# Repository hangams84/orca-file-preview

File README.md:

[한국어](README.md) · [English](README.en.md) · [简体中文](README.zh-CN.md) · [繁體中文](README.zh-TW.md) · [日本語](README.ja.md) · [Deutsch](README.de.md) · [Français](README.fr.md) · [Español](README.es.md) · [Português (Brasil)](README.pt-BR.md) · [Русский](README.ru.md) · [Türkçe](README.tr.md)

# File Preview for Orca

File Preview는 [Orca](https://github.com/stablyai/orca) 안에서 Office · 한글 · PDF · 텍스트 · 이미지 · 3D · CAD · 전자 설계 파일을
**읽기 전용으로 미리 보여 주는** 플러그인입니다. Orca 데스크톱(Windows · macOS · Linux)과 브라우저/모바일 클라이언트에서 동작합니다.

- 최신 릴리스: **v0.4.0** · Orca **1.4.248** 이상 필요 (Git URL 설치는 **1.4.252** 이상)
- `sandboxed-ui` 방식으로만 실행됩니다. 추가 권한(capability)이나 네트워크 접근을 사용하지 않으며, 파일을 수정하지도 않습니다.

## 지원 형식

| 형식 | 확장자 | 엔진 · 표시 내용 |
| --- | --- | --- |
| Word | `.docx` `.doc` | docx-preview · 자체 OLE/CFB 파서 (RTF·HTML·DOCX로 저장된 `.doc` 자동 감지) |
| PowerPoint | `.pptx` `.ppt` | 자체 OOXML 렌더러 · 자체 PPT 레코드 파서 |
| Excel | `.xlsx` `.xlsm` `.xls` `.ods` | SheetJS CE (Web Worker, 수식 계산 대체, 가상 스크롤) |
| 한글 문서 | `.hwp` `.hwpx` | HWP 5 · HWPX(OWPML)를 한글이 저장한 줄 배치대로 표시. 배포용·암호 문서와 HWP 3은 안내 메시지 표시 |
| PDF | `.pdf` | pdf.js (지연 렌더링, 한글 CMap, 암호 입력) |
| 이미지 | `.gif` `.bmp` `.svg` | 브라우저 디코더 (SVG 스크립트 차단, 배경 선택) |
| 웹 | `.html` `.htm` `.xhtml` | DOMPurify + 샌드박스 iframe (스크립트 미실행) |
| 표 | `.csv` `.tsv` | 자체 RFC 4180 파서 (인코딩·구분자 감지, 정렬, 필터) |
| 텍스트 | `.txt` `.log` | 인코딩 감지 (UTF-8/16, EUC-KR 등), 줄 번호, 자동 줄바꿈 |
| 다이어그램 | `.drawio` `.dio` `.vsdx` `.vsdm` `.vstx` `.vssx` | 자체 SVG 렌더러: draw.io(압축·여러 페이지, 기본 도형·연결선·스타일, HTML 레이블은 DOMPurify로 정제), Visio(마스터·스타일 시트 상속, Geometry 행 전체, 그룹·연결선·텍스트 서식·채우기 패턴·그라데이션·테마·EMF/WMF 그림·배경 페이지). 페이지 선택, 이동·확대·맞춤, 어두운 캔버스, 링크 |
| 3D 모델 | `.stl` `.obj` `.ply` `.glb` `.gltf` `.3mf` `.off` `.fbx` `.dae` | three.js (WebGL, 회전·확대·이동, 터치, Draco·meshopt, Web Worker 파싱). OBJ의 `.mtl`·텍스처, glTF의 외부 `.bin`·이미지, DAE·FBX·3MF 텍스처는 참조 파일(📁 · 끌어 놓기)에서 읽음 |
| CAD (B-rep) | `.step` `.stp` `.stpz` `.iges` `.igs` `.brep` | OpenCascade (occt-import-js, WebAssembly, Web Worker): 어셈블리·부품 목록·색상, 테셀레이션 품질 선택. `.stpz`는 gzip으로 압축한 STEP |
| CAD 2D 도면 | `.dxf` `.dwf` `.dwfx` | 자체 Canvas 2D 렌더러: DXF(ASCII·바이너리, R12–2018+, 블록·치수·해치·MTEXT·한글), DWF(W2D 스트림, 시트, 썸네일 대체), DWFx(XPS 페이지, 내장 글꼴). 레이어 목록, 모형·배치(뷰포트)·시트 선택, 밝은/어두운 배경, 정보 표시줄. DXF 외부 참조(xref)와 IMAGE 엔터티는 참조 파일에서 읽음 (xref 레이어는 `XREF\|레이어`) |
| AutoCAD 도면 (별도 플러그인) | `.dwg` `.dwt` | **File Preview DWG** — [별도 저장소](https://github.com/hangams84/orca-file-preview-dwg), GPL-3.0-or-later, 따로 설치합니다 (Git URL `https://github.com/hangams84/orca-file-preview-dwg.git`, 소스 [dwg-plugin/](dwg-plugin/README.md)). LibreDWG (WebAssembly, Web Worker) + Canvas: 모형/배치, 레이어, 블록, 한글 문자, 치수, 해치 |
| 로봇 모델 (ROS) | `.urdf` `.xacro` | 자체 XML 리더 + xacro 처리기(ROS 2 xacro 2.x 규칙, eval 없는 안전한 식 계산기) + three.js: 기구학 트리, 기본 형상, 원점·재질, 조인트 6종·한계·mimic, 조인트 슬라이더, 외형/충돌/좌표계/조인트 축 표시. `.urdf.xacro`도 엽니다. 메시와 `xacro:include`는 참조 파일에서 읽음 |
| KiCad | `.kicad_sch` `.kicad_pcb` `.kicad_mod` `.kicad_sym` `.kicad_pro` `.kicad_wks` | 자체 S-expression 파서 + SVG 렌더러 (KiCad 6–10, 스트로크 글꼴 newstroke): 회로도, PCB(레이어 표시/숨김, 앞/뒷면 뒤집기), 풋프린트, 심볼 라이브러리, 프로젝트 요약, 패드·핀·넷 정보 툴팁. 프로젝트 폴더를 지정하면 계층 시트 탐색과 사용자 도면 틀 표시 |
| SolidWorks | `.sldprt` `.sldasm` `.slddrw` `.slddrt` `.prtdot` `.asmdot` `.drwdot` | 자체 컨테이너 리더 (2014 이전 OLE/CFB, 2015 이후 형식): 저장된 미리보기 그림, 파트의 표시 메시(3D), **어셈블리 3D**(저장된 배치 + 메시, 없으면 📁로 지정한 파트 파일), 속성·구성·참조 파일·피처 이름·저장 기록 |
| EPLAN Electric P8 | `.edz` `.zw1` `.elk` `.ell` `.elr` `.els` `.ela` `.elp` `.elx` `.zx1` `.ema` `.emp` | 자체 7z(LZMA/LZMA2)·ZIP 리더: EDZ 부품 데이터·그림·PDF 문서, **매크로 그래픽**(PXF: 선·호·곡선·문자, 변형별), 프로젝트 백업의 속성·페이지 설명·**부품 목록**·그림·내용 트리, 링크 파일 + 📁 프로젝트 폴더(`.edb`) |
| AI 모델 (PyTorch) | `.pt` `.pth` `.ckpt` `.chkpt` `.pt2` `.ptl` `.safetensors` | 코드를 **실행하지 않는** 자체 pickle 해석기: state_dict·통째 저장한 모듈·TorchScript·torch.export·Lightning 체크포인트·레거시 pickle, safetensors. 보기 7종(**연산 그래프**·모듈 트리·레이어 표·파라미터 맵·아키텍처 도식(추론)·**텐서 검사기**·체크포인트 정보)과 SVG/PNG/JSON/Markdown 내보내기. File Preview 패널은 범위 읽기로 GB 단위 파일도 열고, 내용으로 판별한 bin·pkl 파일도 엽니다 |
| AI 모델 (ONNX·TFLite·GGUF·Keras·NumPy) | `.onnx` `.tflite` `.gguf` `.keras` `.h5` `.hdf5` `.npy` `.npz` | 같은 보기로 표시: ONNX·TFLite·Keras 연산 그래프, GGUF 메타데이터와 양자화 텐서(Q4_K 등) 값, HDF5·NumPy 배열. ONNX 외부 데이터는 📁 폴더로 연결 |
| (읽을 수 없는 파일) | 위 형식 전체 | 일반 검사기: 형식 식별, 크기, 엔트로피, 16진수 덤프, 문자열 |
| **File Preview 패널** | 위 형식 전체 | 오른쪽 사이드바 패널. 아래 [File Preview 패널](#file-preview-패널) 참고 |

공통: 다크/라이트 테마 실시간 반영, 한국어/영어 UI, Ctrl+휠 · 핀치 · 버튼으로 확대/축소, 휴대폰 화면 폭 맞춤,
파일이 바뀌면 자동 갱신, 손상된 파일은 친절한 오류 안내.

### 텍스트 형식도 바로 미리보기로 열립니다 (0.4.0)

URDF·xacro, KiCad, draw.io, ASCII DXF, STEP·IGES·BREP, OBJ 등 텍스트로 된 3D 형식, RTF/HTML로 저장된 `.doc`,
XML `.xls`는 Orca가 텍스트 파일로 인식합니다. 플러그인이 이러한 파일용 텍스트 편집기를 따로 등록하므로 이제 기본적으로
미리보기로 열립니다. 단, Orca가 직접 여는 형식(`.txt` `.csv` `.tsv` `.html` `.htm`)은 Orca 규칙에 따라 ‘소스’ 보기로 먼저 열립니다.
탭 오른쪽 위의 보기 전환 버튼에서 미리보기를 선택하면 됩니다.

### 참조 파일 (📁 · 끌어 놓기)

Orca는 편집기에 연 파일 하나만 플러그인에 전달합니다. 툴바의 📁 버튼으로 폴더를 선택하거나(Shift를 누른 채 누르면 파일 선택) 파일을 미리보기에
끌어다 놓으면, 플러그인이 샌드박스 프레임 안에서 그 파일들을 함께 읽습니다.

| 미리보기 | 폴더나 파일을 지정하면 추가되는 기능 |
| --- | --- |
| 로봇 (URDF/xacro) | 메시(STL, 텍스처가 있는 DAE, `.mtl`이 있는 OBJ, glTF)가 자리 표시자를 대체하고 조인트 자세는 유지. `xacro:include` 처리(`$(find pkg)`, 상대 경로, 중첩) |
| 3D | OBJ 재질과 텍스처, glTF 외부 `.bin`과 이미지, DAE 텍스처 |
| CAD 도면 (DXF) | 외부 참조(xref)를 `XREF\|레이어`로 삽입, IMAGE 엔터티 표시 |
| KiCad | 하위 시트 탐색(인스턴스별 참조 기호), `.kicad_pro` → 회로도·보드, 사용자 `.kicad_wks` |
| SolidWorks | 저장된 배치로 **어셈블리 3D** 표시 (2015 이후 파일은 파트 파일 불필요, 2014 파일은 지정한 파트 파일 사용) |
| EPLAN | 매크로 그래픽 표시(`.ema` `.emp`, `.edz` 안의 매크로), `.elk` + `.edb` 폴더 → 프로젝트 속성, 페이지, 부품 목록 |

### File Preview 패널

오른쪽 사이드바의 **File Preview** 패널에서 "파일 열기…", "폴더 열기…" 또는 끌어 놓기로 파일을 열면 같은 렌더러로 표시합니다.
Orca 편집기의 50 MB 한도가 적용되지 않으며(렌더러 자체 한도만 적용, 최대 1 GB) 워크스페이스 밖의 파일도 열 수 있습니다. 함께 연 파일은
참조 파일로 사용됩니다. 추가 권한은 필요하지 않습니다.

## 설치

### (a) Orca 앱에서 설치 (권장)

Orca **1.4.252** 이상에서 사용할 수 있습니다.

1. **설정** → **플러그인**을 엽니다.
2. **플러그인 추가** → **Git URL에서…**를 선택합니다.
3. **저장소 URL**에 `https://github.com/hangams84/orca-file-preview.git`을 붙여 넣고 **계속** → **설치**를 누릅니다.
4. Orca가 보여 주는 권한(샌드박스 화면 표시만)을 확인하고 **플러그인 활성화**를 누릅니다.

화면별 안내: [docs/install-guide/ko.md](docs/install-guide/ko.md)

<!-- install-guide-thumbs -->

`.dwg` · `.dwt` 미리보기가 필요하면 같은 방법으로 `https://github.com/hangams84/orca-file-preview-dwg.git`도 설치합니다.

### (b) CLI로 설치

```sh
# GitHub에서 최신 버전 설치 (Orca 1.4.252+). Orca가 요청 권한과 승인 지문을 출력합니다.
orca plugin install https://github.com/hangams84/orca-file-preview
orca plugin install https://github.com/hangams84/orca-file-preview --approve <fingerprint>
# 특정 버전: https://github.com/hangams84/orca-file-preview#v0.5.0

# 또는 로컬 폴더
orca plugin install ./plugin
```

### (c) 릴리스 패키지 · 실행 파일 · 스크립트

[GitHub Releases](https://github.com/hangams84/orca-file-preview/releases)에서 내려받습니다. Orca 1.4.248 이상이 설치되어 있고
한 번 이상 실행된 PC가 필요하며, 관리자 권한은 필요 없습니다. 모든 설치 프로그램은 Orca가 요청하는 권한을 보여 주고,
사용자가 확인한 뒤에만 승인합니다.

| OS | 실행 파일 | 스크립트 (zip · tar.gz 패키지) |
| --- | --- | --- |
| Windows 10/11 | `FilePreviewSetup-<버전>.exe` (메뉴: 설치 · 업데이트 · 제거 · 상태) | `installer\windows\install.cmd` |
| macOS | `File-Preview-Setup-<버전>-macos.zip` → *File Preview Setup.app* | `installer/macos/Install File Preview.command` |
| macOS · Linux | `sh file-preview-setup-<버전>.run [install\|update\|uninstall\|status]` | `sh installer/linux/install.sh` (Linux) |

실행 파일은 코드 서명이 되어 있지 않습니다. Windows SmartScreen이 차단하면 *추가 정보* → *실행*을, macOS Gatekeeper가 차단하면 Control-클릭 → *열기*를 선택합니다.
Orca 1.4.248–1.4.251에는 `plugin install`이 없어 설치 스크립트가 개발 폴더 등록(`plugin dev load`) 방식으로 설치합니다. 이 경우 해당 폴더를 삭제하지 마세요.
Windows 7/8은 Orca가 지원하지 않으므로 설치 프로그램이 안내 메시지를 표시하고 설치를 거부합니다(Windows 10 이상 필요).
자세한 옵션: [installer/README.md](installer/README.md)

### (d) 업데이트와 제거

- **Orca 앱·CLI로 설치한 경우**: `orca plugin list`로 플러그인 키를 확인한 뒤 `orca plugin update <키>`로 업데이트하고
  `orca plugin uninstall <키>`로 제거합니다. Git URL로 설치한 경우 업데이트하면 최신 버전 태그로 이동합니다.
- **실행 파일**: `FilePreviewSetup-<버전>.exe`의 메뉴(또는 `/update` · `/uninstall`), `file-preview-setup-<버전>.run update|uninstall`,
  macOS는 *File Preview Setup.app*에서 선택합니다.
- **스크립트**: Windows `installer\windows\update.cmd` · `uninstall.cmd`, macOS `Update File Preview.command` ·
  `Uninstall File Preview.command`, Linux `sh installer/linux/update.sh` · `sh installer/linux/uninstall.sh`.
- 업데이트는 이 저장소의 최신 GitHub 릴리스를 확인하고, 패키지를 내려받아 SHA-256을 검증한 뒤 승인을 거쳐 다시 설치합니다.
  직전 버전 하나를 보관합니다. `--check`(Windows `-Check`)는 업데이트 여부만 확인합니다.

## 제한 사항

- **50 MB 읽기 한도**: Orca는 플러그인 편집기에 파일을 최대 50 MB까지만 전달합니다(이미지·PDF 제외, 플러그인에서 바꿀 수 없음,
  [stablyai/orca#46775](https://github.com/stablyai/orca/issues/46775)). 플러그인 자체 한도는 1 GB입니다. 더 큰 파일은
  [File Preview 패널](#file-preview-패널)로 여세요. STEP 파일은 gzip으로 압축해 `.stpz`로 열 수도 있습니다(보통 5–8배 줄어듭니다):
  `gzip -c model.step > model.stpz`.
- **CAD 엔진 크기**: OpenCascade(32비트 WebAssembly, 최대 4 GB 메모리)의 실질적인 상한은 STEP 원본 기준 약 200 MB입니다.
  실측(부품이 많은 합성 어셈블리): 61 MB 1.5분 · 189 MB 14분 · 343 MB는 30분 안에 끝나지 않음 · 412 MB는 메모리 부족.
- **‘소스’ 보기로 먼저 열리는 형식**: `.txt` `.csv` `.tsv` `.html` `.htm`은 Orca가 직접 여는 형식이라 ‘소스’ 보기가 먼저 열립니다.
  미리보기는 보기 전환 버튼에서 선택합니다.
- **표시하지 않는 내용**:
  - EPLAN: 회로도 페이지(EPLAN 고유 바이너리 객체 저장소 `.eod`/`.eox`)와 심볼 라이브러리 그래픽.
  - SolidWorks: 정확한 B-rep 형상과 도면 뷰는 다시 그리지 않고 저장된 그림을 보여 줍니다. 숨김·억제된 구성 요소는 목록에만 표시됩니다.
  - draw.io: 내장되지 않은 스텐실 라이브러리(`mxgraph.aws4.*` 등)는 이름이 적힌 점선 상자로, 원격 그림은 자리 표시자로 표시됩니다.
  - Visio: 수식은 계산하지 않고 저장된 값을 씁니다. 바이너리 `.vsd`는 지원하지 않습니다(안내 메시지).
  - DWF: 해석할 수 없는 명령이 포함된 시트는 패키지에 저장된 썸네일과 안내 메시지를 보여 줍니다.
  - DWG(별도 플러그인): 3D 솔리드·영역(ACIS), 래스터 이미지 내용, OLE, xref는 그리지 않고 목록으로 알립니다.
  - Office: PPTX의 차트·SmartArt와 스프레드시트의 셀 스타일은 단순화해 표시하며, 스프레드시트는 처음 20,000행만 보여 줍니다.
    `.hwp`의 수식·차트·OLE 개체는 이름이 붙은 상자로 표시합니다.
- 모바일 클라이언트는 실제 기기가 아니라 브라우저 하네스(휴대폰 프로필, WebKit, 구형 엔진 모드)로 테스트했습니다.

## Orca 버전별 호환성 (CI)

아래 표는 `.github/workflows/orca-compat.yml`이 각 Orca 릴리스를 새로 설치한 뒤 플러그인을 설치하고 테스트한 결과입니다.
플러그인, 설치 스크립트, 테스트 도구의 변경 사항이 `main`에 푸시되면 워크플로가 자동으로 실행되고 표도 함께 갱신됩니다.

<!-- ci-matrix:start -->
**Orca compatibility CI** — ✅ all passing · 2026-11-27 10:45 UTC · [run](https://github.com/hangams84/orca-file-preview/actions/runs/45981742783)

| Orca | Ubuntu 24.04 (Docker) | Ubuntu 26.04 (Docker) | macOS 15 arm64 | Windows 10 kernel (Server 2022) | Windows 11 kernel (Server 2025) |
| --- | --- | --- | --- | --- | --- |
| 1.4.277 | ✅ 9/9 | ✅ 9/9 | ✅ 12/12 | ✅ 10/10 | ✅ 10/10 |
| 1.4.258 | ✅ 9/9 | ✅ 9/9 | ✅ 12/12 | ✅ 10/10 | ✅ 10/10 |
| 1.4.257 | ✅ 9/9 | — | — | — | — |
| 1.4.256 | ✅ 9/9 | — | — | — | — |
| 1.4.255 | ✅ 9/9 | — | — | — | — |
| 1.4.254 | ✅ 9/9 | — | — | — | — |
| 1.4.253 | ✅ 9/9 | ✅ 9/9 | ✅ 12/12 | ✅ 10/10 | ✅ 10/10 |
| 1.4.252 | ✅ 9/9 | — | — | — | — |
| 1.4.251 | ✅ 9/9 | — | — | — | — |
| 1.4.250 | ✅ 9/9 | — | — | — | — |
| 1.4.249 | ✅ 9/9 | — | — | — | — |
| 1.4.248 | ✅ 9/9 | ✅ 9/9 | ✅ 12/12 | ✅ 10/10 | ✅ 10/10 |
| 1.4.247 (below min, informational) | ✅ 9/9 | — | — | — | — |

Windows 7: ✅ the installer refuses with a clear message — Orca (Electron 23+) needs Windows 10 or later, and no Windows 7 CI runners exist. Windows 10/11 columns run on GitHub's Windows Server images, which share the Windows 10 (build 20348) and Windows 11 24H2 (build 26100) kernels; Windows 11 Pro 26200 was also tested on a real PC.

Each cell: a fresh Orca install of that version → plugin install with approval → validate · unit tests · static check → every fixture opened in the plugin editor → finished renders captured → plugin log free of errors (Windows also installs and removes through `installer/windows`). 1.4.247 is below the declared minimum (`engines.orca` >=1.4.248): Orca does not enforce that for folder installs, so its row is informational.
<!-- ci-matrix:end -->

### 운영체제별 테스트

실제 Orca(1.4.258)를 새로 설치하고 플러그인 설치 → 검사 → 단위 테스트 → 전체 픽스처 마운트 → 렌더 캡처를 수행합니다.

| 환경 | 실행 | 결과 |
| --- | --- | --- |
| Ubuntu 22.04 / 24.04 / 26.04 | `bash tools/platform-test/run-docker.sh 22.04 24.04 26.04` (WSL2 또는 Linux의 Docker, Xvfb) | 9/9 · 9/9 · 9/9 (26.04.1, Orca 1.4.277) |
| macOS 15 (arm64) | GitHub Actions `platform-macos` 워크플로 (`gh workflow run platform-macos --ref ci/macos-orca`) | 12/12 |
| Windows 11 | `node tools/verify.mjs --round <n>` (설치된 Orca 앱) | 10/10 |

증빙: `docs/evidence/platforms/` (summary.md, contact-sheet.png, 캡처, 로그)

## 개발

```sh
npm ci
npm run vendor            # 서드파티 라이브러리를 plugin/vendor로 번들
orca plugin dev load plugin --approve <fingerprint>
npm run typecheck
node tools/harness/run.mjs --only docx,pdf --profiles desktop-dark,mobile-light
node tools/verify.mjs --round <n> && node tools/build-docs.mjs
node tools/check-readmes.mjs   # README 11개 언어의 언어 표시줄·링크·형식 표 검사
```

### 저장소 구조

```text
plugin/            배포되는 플러그인 (orca-plugin.json, editor/, panel/, vendor/)
dwg-plugin/        File Preview DWG 소스 (GPL-3.0-or-later, 별도 플러그인)
installer/         Windows · macOS · Linux 설치 스크립트
samples/           테스트 픽스처 (tools/make-samples.py 등)
tools/harness/     Orca와 같은 CSP + 모의 호스트 브라우저 하네스 (Playwright)
tools/verify.mjs   검증 라운드 실행기 (tsc, validate, 단위 테스트, 하네스 4종, fuzz, Orca 앱 캡처)
docs/              개발·검증 문서 (README.md, index.html, evidence/, release-notes/)
```

검증 기록과 스크린샷은 [docs/README.md](docs/README.md) · [docs/index.html](docs/index.html)에, 변경 내역은 [CHANGELOG.md](CHANGELOG.md)에 있습니다.

## 라이선스

이 프로젝트는 MIT 라이선스로 배포됩니다([LICENSE](LICENSE)). 번들된 라이브러리는 각각의 라이선스를 따릅니다:
[plugin/THIRD_PARTY_NOTICES.md](plugin/THIRD_PARTY_NOTICES.md).
`.dwg` · `.dwt`용 **File Preview DWG**는 GPL-3.0-or-later인 별도 플러그인이며 이 MIT 플러그인에 포함되지 않습니다.

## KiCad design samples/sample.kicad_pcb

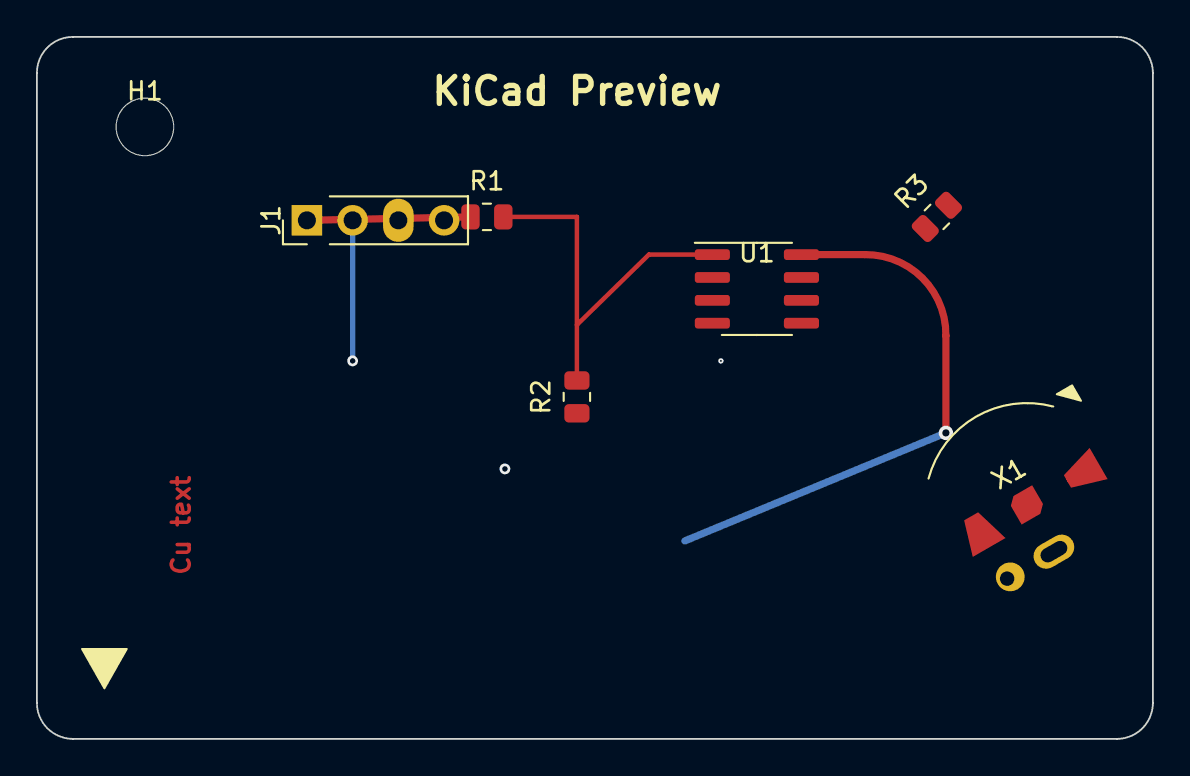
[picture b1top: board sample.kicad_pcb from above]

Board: 4 copper layers, 62.0 x 39.0 mm, 8 parts (1 on the bottom side), 4 nets.

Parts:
C1: 10k; R_0805_2012Metric
H1: M3; MountingHole_3.2mm_M3
J1: Conn; PinHeader_1x04_P2.54mm_Vertical
R1, R2, R3: 10k; R_0805_2012Metric
U1: MCU; SOIC-8_3.9x4.9mm_P1.27mm
X1: ODD; OddPads

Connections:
+5V: C1.2, J1.1, R1.1, R3.2, U1.8
GND: C1.1, J1.2, R2.2, U1.4, X1.4, X1.5
SDA: J1.3, R3.1, U1.5, U1.6, U1.7
SIG: R1.2, R2.1, U1.1, U1.2, U1.3, X1.1, X1.2, X1.3
